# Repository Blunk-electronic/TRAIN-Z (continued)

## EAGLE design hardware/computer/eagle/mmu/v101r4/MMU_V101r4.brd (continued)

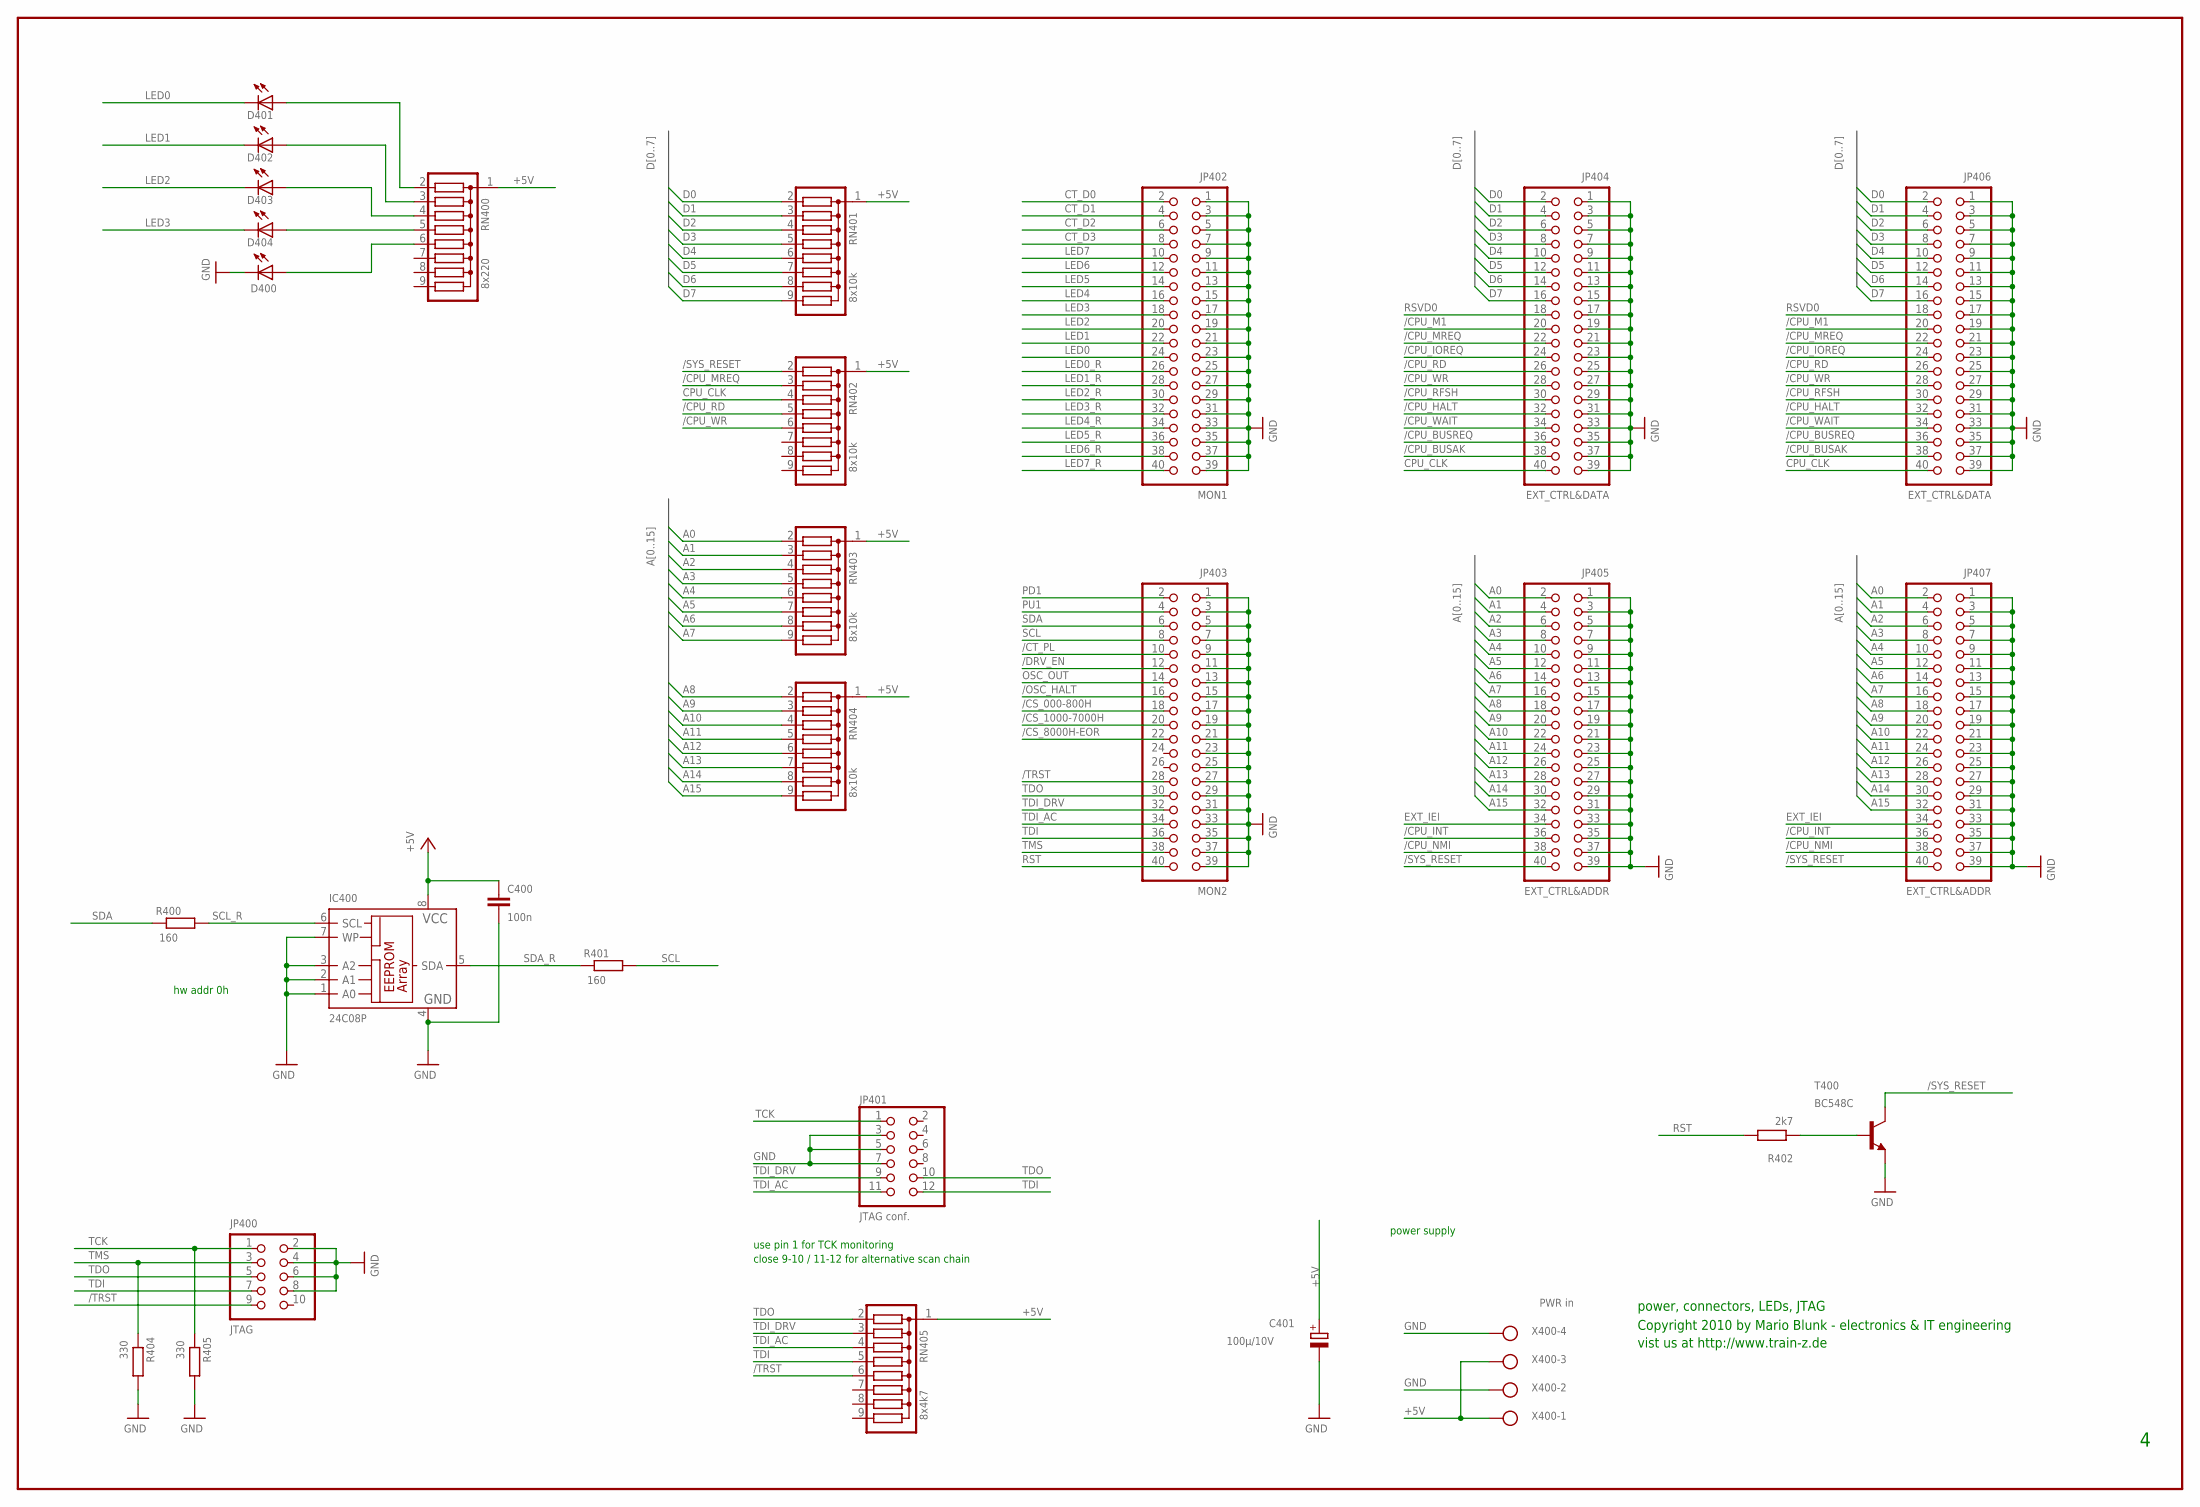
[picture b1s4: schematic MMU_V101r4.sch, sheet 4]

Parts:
C400: 100n; C050-030X075
C401: 100µ/10V; E2,5-7
D400, D401, D402, D403, D404: LED5MM
IC400: 24C08P; DIL8
JP400: JTAG; 2X05
JP401: JTAG conf.; 2X06
JP402: MON1; 2X20
JP403: MON2; 2X20
JP404, JP406: EXT_CTRL&DATA; 2X20
JP405, JP407: EXT_CTRL&ADDR; 2X20
R400, R401: 160; 0207/10
R402: 2k7; 0207/10
R404, R405: 330; 0207/10
RN400: 8x220; SIL9
RN401, RN402, RN403, RN404: 8x10k; SIL9
RN405: 8x4k7; SIL9
T400: BC548C; TO92
X400: PWR in; W237-4

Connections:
+5V: C400.1, C401.+, IC400.8 (VCC), RN400.1, RN401.1, RN402.1, RN403.1, RN404.1, RN405.1, X400.1, X400.3; also elsewhere on the board
/CPU_BUSAK: JP404.38, JP406.38
/CPU_BUSREQ: JP404.36, JP406.36
/CPU_HALT: JP404.32, JP406.32
/CPU_INT: JP405.36, JP407.36
/CPU_IOREQ: JP404.24, JP406.24
/CPU_M1: JP404.20, JP406.20
/CPU_MREQ: JP404.22, JP406.22, RN402.3; also elsewhere on the board
/CPU_NMI: JP405.38, JP407.38
/CPU_RD: JP404.26, JP406.26, RN402.5; also elsewhere on the board
/CPU_RFSH: JP404.30, JP406.30
/CPU_WAIT: JP404.34, JP406.34
/CPU_WR: JP404.28, JP406.28, RN402.6; also elsewhere on the board
/CS_000-800H: JP403.18; also elsewhere on the board
/CS_1000-7000H: JP403.20; also elsewhere on the board
/CS_8000H-EOR: JP403.22; also elsewhere on the board
/CT_PL: JP403.10; also elsewhere on the board
/DRV_EN: JP403.12; also elsewhere on the board
/OSC_HALT: JP403.16; also elsewhere on the board
/SYS_RESET: JP405.40, JP407.40, RN402.2, T400.3 (C); also elsewhere on the board
/TRST: JP400.9, JP403.28, RN405.6
A0: JP405.2, JP407.2, RN403.2; also elsewhere on the board
A1: JP405.4, JP407.4, RN403.3; also elsewhere on the board
A2: JP405.6, JP407.6, RN403.4; also elsewhere on the board
A3: JP405.8, JP407.8, RN403.5; also elsewhere on the board
A4: JP405.10, JP407.10, RN403.6; also elsewhere on the board
A5: JP405.12, JP407.12, RN403.7; also elsewhere on the board
A6: JP405.14, JP407.14, RN403.8; also elsewhere on the board
A7: JP405.16, JP407.16, RN403.9; also elsewhere on the board
A8: JP405.18, JP407.18, RN404.2; also elsewhere on the board
A9: JP405.20, JP407.20, RN404.3; also elsewhere on the board
A10: JP405.22, JP407.22, RN404.4; also elsewhere on the board
A11: JP405.24, JP407.24, RN404.5; also elsewhere on the board
A12: JP405.26, JP407.26, RN404.6; also elsewhere on the board
A13: JP405.28, JP407.28, RN404.7; also elsewhere on the board
A14: JP405.30, JP407.30, RN404.8; also elsewhere on the board
A15: JP405.32, JP407.32, RN404.9; also elsewhere on the board
CPU_CLK: JP404.40, JP406.40, RN402.4; also elsewhere on the board
CT_D0: JP402.2; also elsewhere on the board
CT_D1: JP402.4; also elsewhere on the board
CT_D2: JP402.6; also elsewhere on the board
CT_D3: JP402.8; also elsewhere on the board
D0: JP404.2, JP406.2, RN401.2; also elsewhere on the board
D1: JP404.4, JP406.4, RN401.3; also elsewhere on the board
D2: JP404.6, JP406.6, RN401.4; also elsewhere on the board
D3: JP404.8, JP406.8, RN401.5; also elsewhere on the board
D4: JP404.10, JP406.10, RN401.6; also elsewhere on the board
D4_A: D400.A, RN400.6
D5: JP404.12, JP406.12, RN401.7; also elsewhere on the board
D6: JP404.14, JP406.14, RN401.8; also elsewhere on the board
D7: JP404.16, JP406.16, RN401.9; also elsewhere on the board
EXT_IEI: JP405.34, JP407.34
GND: C400.2, C401.-, D400.K (C), IC400.1 (A0), IC400.2 (A1), IC400.3 (A2), IC400.4 (GND), IC400.7 (WP), JP400.2, JP400.4, JP400.6, JP400.8, JP401.3, JP401.5, JP401.7, JP402.1, JP402.3, JP402.5, JP402.7, JP402.9, JP402.11, JP402.13, JP402.15, JP402.17, JP402.19, JP402.21, JP402.23, JP402.25, JP402.27, JP402.29, JP402.31, JP402.33, JP402.35, JP402.37, JP402.39, JP403.1, JP403.3, JP403.5, JP403.7, JP403.9, JP403.11, JP403.13, JP403.15, JP403.17, JP403.19, JP403.21, JP403.23, JP403.25, JP403.27, JP403.29, JP403.31, JP403.33, JP403.35, JP403.37, JP403.39, JP404.1, JP404.3, JP404.5, JP404.7, JP404.9, JP404.11, JP404.13, JP404.15, JP404.17, JP404.19, JP404.21, JP404.23, JP404.25, JP404.27, JP404.29, JP404.31, JP404.33, JP404.35, JP404.37, JP404.39, JP405.1, JP405.3, JP405.5, JP405.7, JP405.9, JP405.11, JP405.13, JP405.15, JP405.17, JP405.19, JP405.21, JP405.23, JP405.25, JP405.27, JP405.29, JP405.31, JP405.33, JP405.35, JP405.37, JP405.39, JP406.1, JP406.3, JP406.5, JP406.7, JP406.9, JP406.11, JP406.13, JP406.15, JP406.17, JP406.19, JP406.21, JP406.23, JP406.25, JP406.27, JP406.29, JP406.31, JP406.33, JP406.35, JP406.37, JP406.39, JP407.1, JP407.3, JP407.5, JP407.7, JP407.9, JP407.11, JP407.13, JP407.15, JP407.17, JP407.19, JP407.21, JP407.23, JP407.25, JP407.27, JP407.29, JP407.31, JP407.33, JP407.35, JP407.37, JP407.39, R404.2, R405.2, T400.1 (E), X400.2, X400.4; also elsewhere on the board
LED0: D401.K (C), JP402.24; also elsewhere on the board
LED0_K: D401.A, RN400.2
LED0_R: JP402.26; also elsewhere on the board
LED1: D402.K (C), JP402.22; also elsewhere on the board
LED1_K: D402.A, RN400.3
LED1_R: JP402.28; also elsewhere on the board
LED2: D403.K (C), JP402.20; also elsewhere on the board
LED2_K: D403.A, RN400.4
LED2_R: JP402.30; also elsewhere on the board
LED3: D404.K (C), JP402.18; also elsewhere on the board
LED3_K: D404.A, RN400.5
LED3_R: JP402.32; also elsewhere on the board
LED4: JP402.16; also elsewhere on the board
LED4_R: JP402.34; also elsewhere on the board
LED5: JP402.14; also elsewhere on the board
LED5_R: JP402.36; also elsewhere on the board
LED6: JP402.12; also elsewhere on the board
LED6_R: JP402.38; also elsewhere on the board
LED7: JP402.10; also elsewhere on the board
LED7_R: JP402.40; also elsewhere on the board
OSC_OUT: JP403.14; also elsewhere on the board
PD1: JP403.2; also elsewhere on the board
PU1: JP403.4; also elsewhere on the board
RST: JP403.40, R402.2; also elsewhere on the board
RSVD0: JP404.18, JP406.18
SCL: JP403.8, R401.2; also elsewhere on the board
SCL_R: IC400.6 (SCL), R400.2
SDA: JP403.6, R400.1; also elsewhere on the board
SDA_R: IC400.5 (SDA), R401.1
T2_B: R402.1, T400.2 (B)
TCK: JP400.1, JP401.1, R405.1; also elsewhere on the board
TDI: JP400.7, JP401.12, JP403.36, RN405.5; also elsewhere on the board
TDI_AC: JP401.11, JP403.34, RN405.4; also elsewhere on the board
TDI_DRV: JP401.9, JP403.32, RN405.3; also elsewhere on the board
TDO: JP400.5, JP401.10, JP403.30, RN405.2; also elsewhere on the board
TMS: JP400.3, JP403.38, R404.1; also elsewhere on the board

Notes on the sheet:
power, connectors, LEDs, JTAG
power supply
hw addr 0h
close 9-10 / 11-12 for alternative scan chain
use pin 1 for TCK monitoring
Copyright 2010 by Mario Blunk - electronics & IT engineering
vist us at http://www.train-z.de

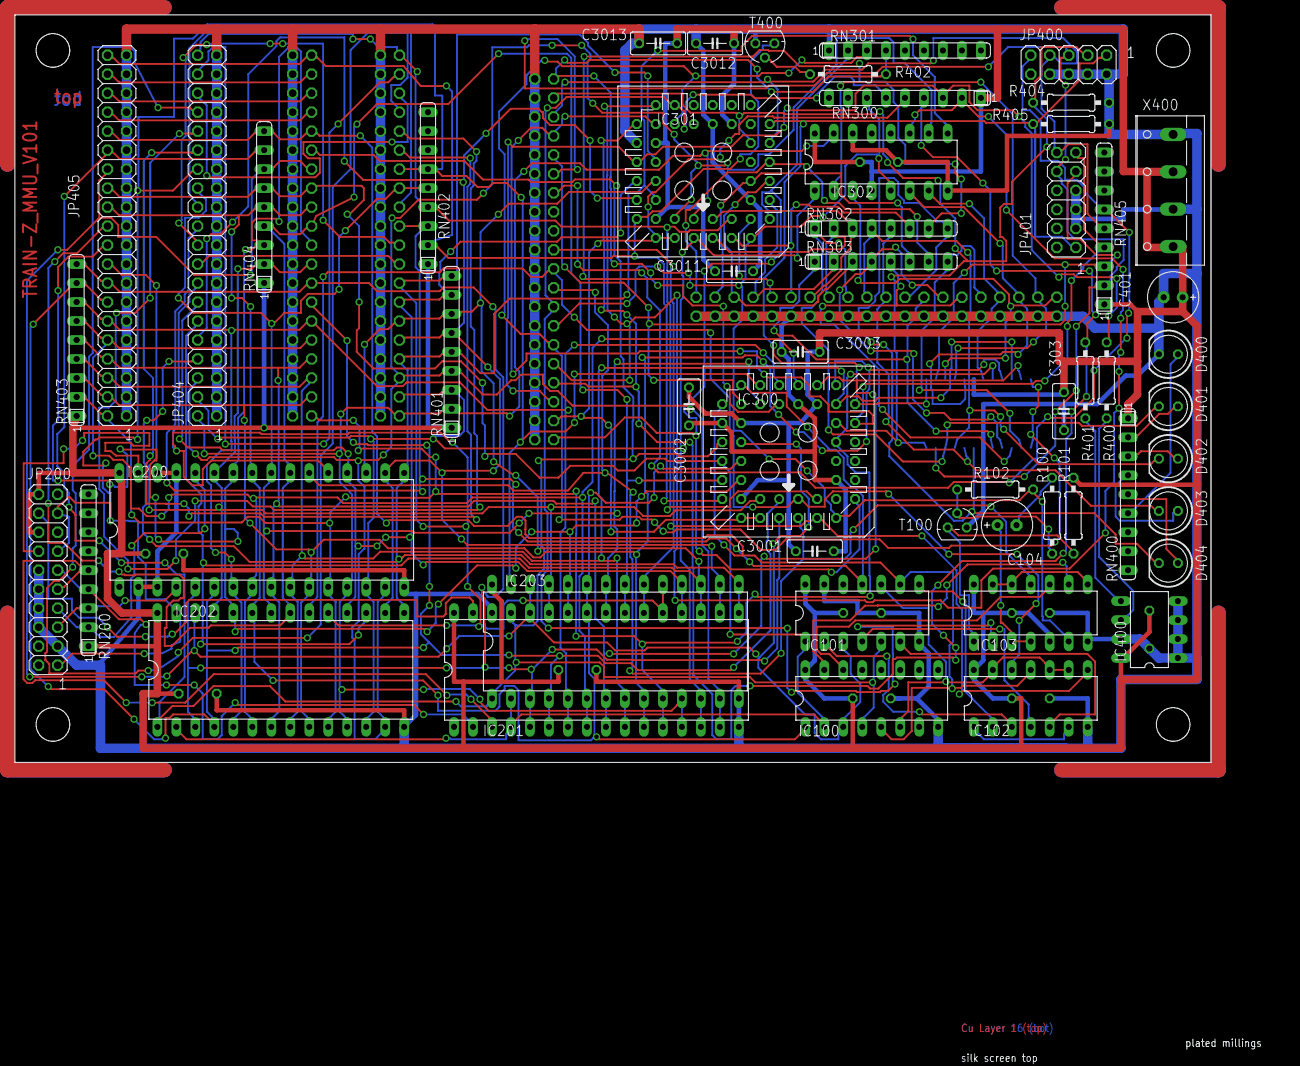
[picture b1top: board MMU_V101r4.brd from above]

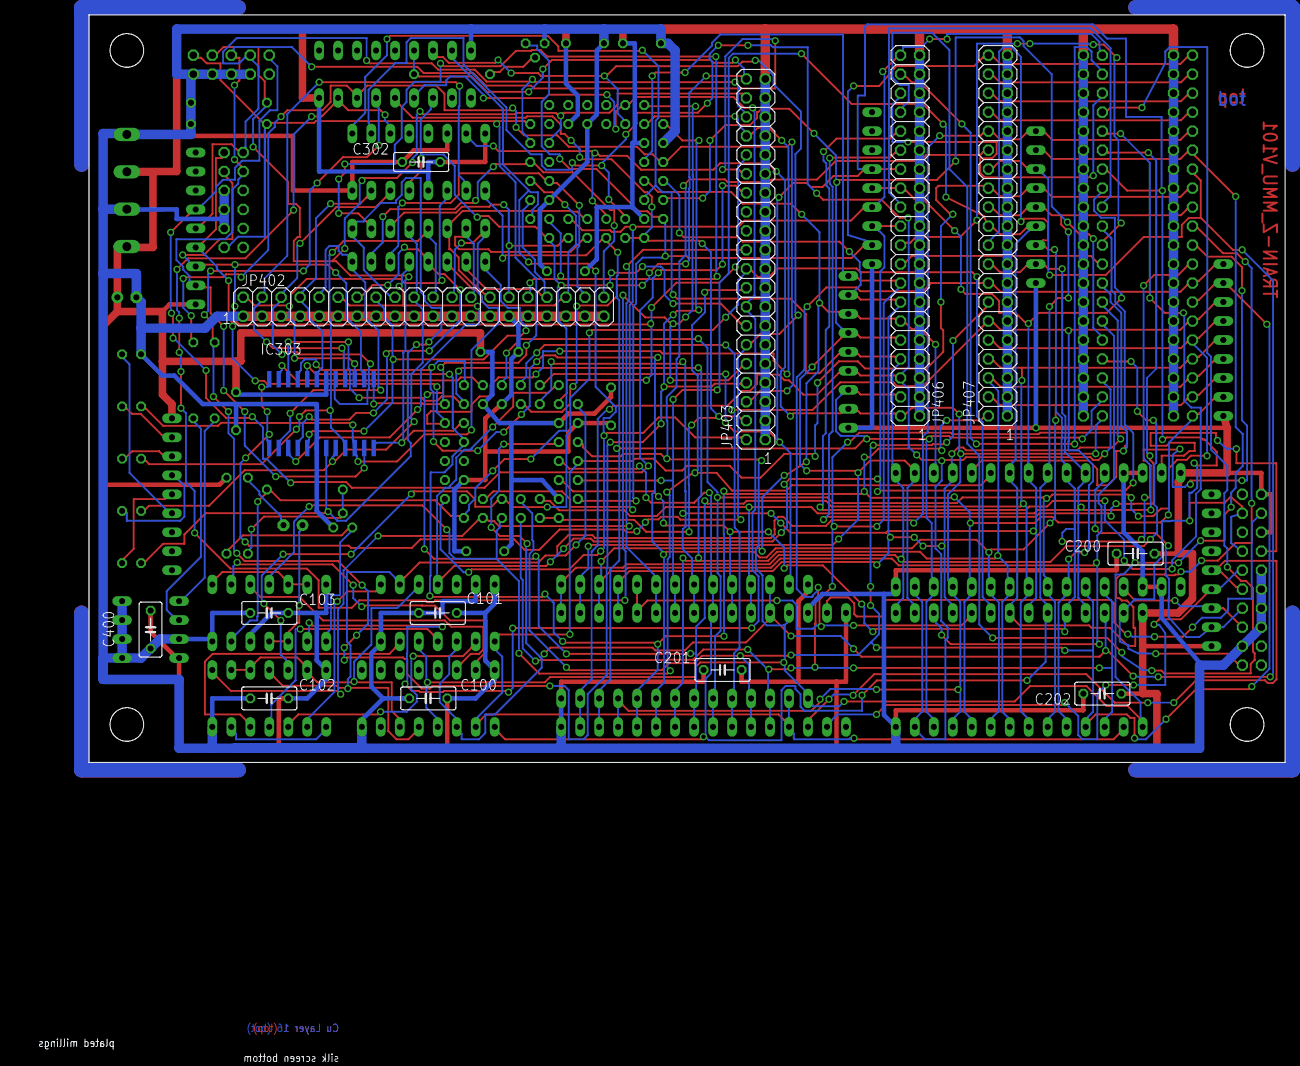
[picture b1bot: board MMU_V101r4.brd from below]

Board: 2 copper layers, 160.0 x 100.0 mm, 68 parts (14 on the bottom side), 108 nets.

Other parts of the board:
U$1: A4_LANDSCAPE

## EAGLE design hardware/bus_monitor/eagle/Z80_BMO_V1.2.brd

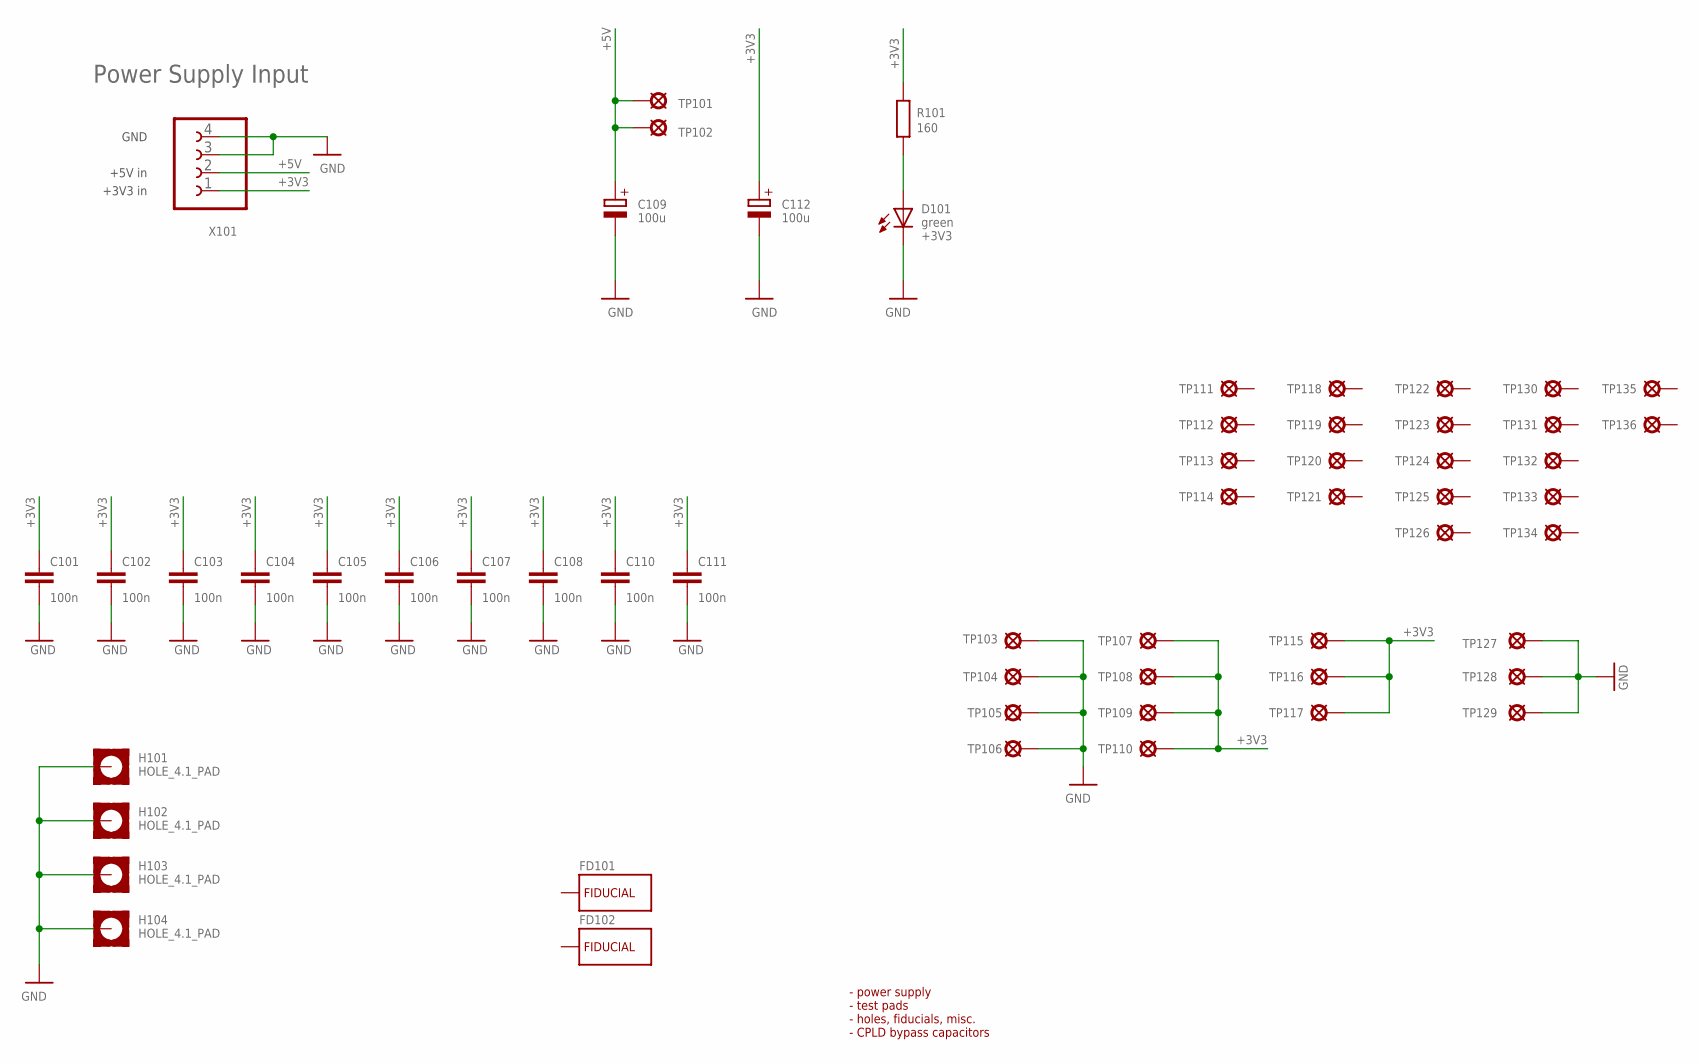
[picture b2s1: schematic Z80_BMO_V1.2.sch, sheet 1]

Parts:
C101, C102, C103, C104, C105, C106, C107, C108, C110, C111: 100n; S_0805; PART_CODE_BEL C_PAC_S_0805_VAL_100n
C109, C112: 100u; T_RADIAL_7MM_GRID_2.54MM; PART_CODE_BEL C_PAC_T_RADIAL_7mm_GRID_2.54mm_VAL_100u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
D101: green; T_LED_3MM; PART_CODE_BEL LED_PAC_T_3mm_VAL_green
FD101, FD102: FIDUCIAL_CROSSHAIR; CROSSHAIR
H101, H102, H103, H104: HOLE_4.1_PAD; 4.1_PAD
R101: 160; T_0207_GRID10MM; PART_CODE_BEL R_PAC_T_0207_GRID10mm_VAL_160
TP101, TP102, TP103, TP104, TP105, TP106, TP107, TP108, TP109, TP110, TP111, TP112, TP113, TP114, TP115, TP116, TP117, TP118, TP119, TP120, TP121, TP122, TP123, TP124, TP125, TP126, TP127, TP128, TP129, TP130, TP131, TP132, TP133, TP134, TP135, TP136: TEST_POINT_T_SMALL; T_TEST_POINT_SMALL
X101: CLAMP_1X4-T-5MM; T_WIRE_CLAMP_1X4_5MM

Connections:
3V3_LED_A: D101.A, R101.1
+3V3: C101.1, C102.1, C103.1, C104.1, C105.1, C106.1, C107.1, C108.1, C110.1, C111.1, C112.+, R101.2, TP107.1, TP108.1, TP109.1, TP110.1, TP115.1, TP116.1, TP117.1, X101.1; also elsewhere on the board
+5V: C109.+, TP101.1, TP102.1, X101.2
GND: C101.2, C102.2, C103.2, C104.2, C105.2, C106.2, C107.2, C108.2, C109.-, C110.2, C111.2, C112.-, D101.C, H101.H1, H102.H1, H103.H1, H104.H1, TP103.1, TP104.1, TP105.1, TP106.1, TP127.1, TP128.1, TP129.1, X101.3, X101.4; also elsewhere on the board

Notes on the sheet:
+3V3 in
+5V in
GND
- power supply - test pads - holes, fiducials, misc. - CPLD bypass capacitors

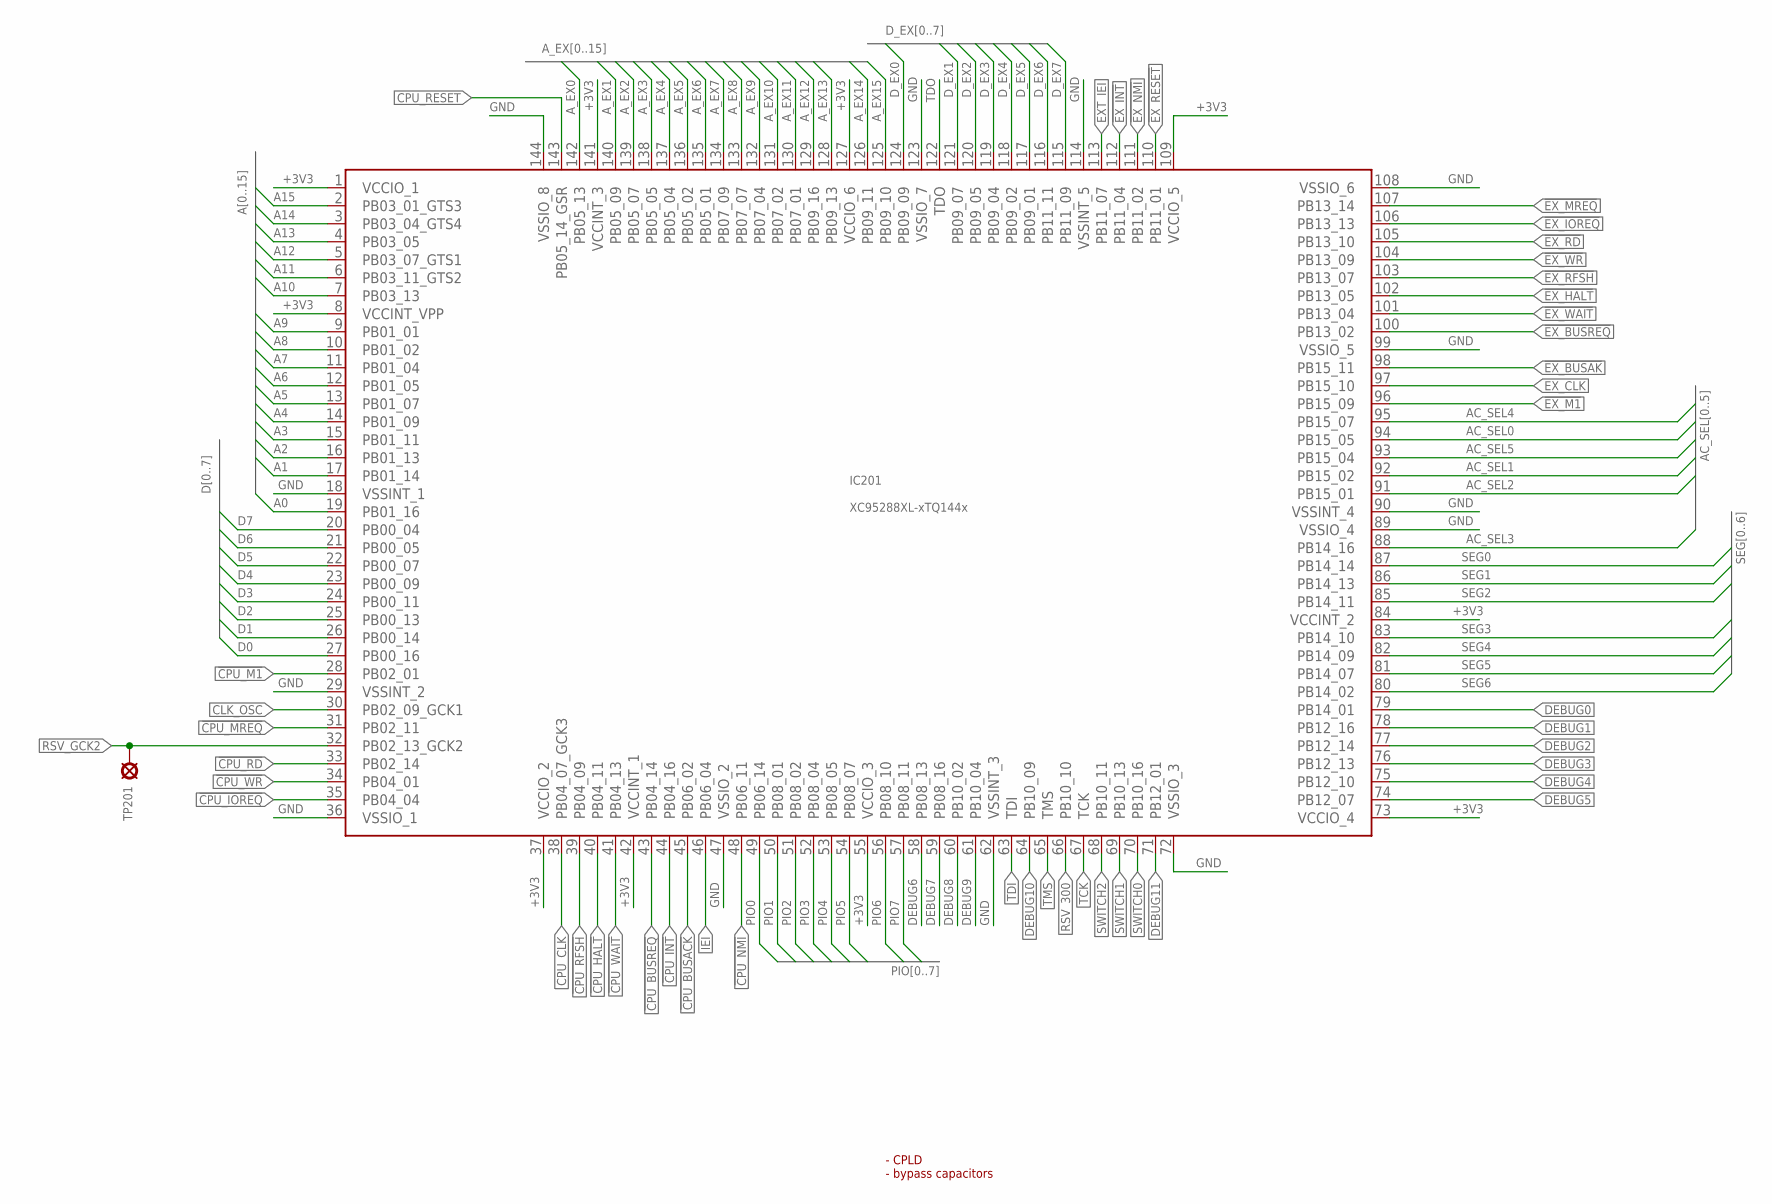
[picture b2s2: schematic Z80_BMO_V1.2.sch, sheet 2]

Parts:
IC201: XC95288XL-xTQ144x; S_TQFP144
TP201: TEST_POINT_T_SMALL; T_TEST_POINT_SMALL

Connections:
!CPU_BUSACK: IC201.45 (PB06_02); also elsewhere on the board
!CPU_BUSREQ: IC201.43 (PB04_14); also elsewhere on the board
!CPU_HALT: IC201.40 (PB04_11); also elsewhere on the board
!CPU_INT: IC201.44 (PB04_16); also elsewhere on the board
!CPU_IOREQ: IC201.35 (PB04_04); also elsewhere on the board
!CPU_M1: IC201.28 (PB02_01); also elsewhere on the board
!CPU_MREQ: IC201.31 (PB02_11); also elsewhere on the board
!CPU_NMI: IC201.48 (PB06_11); also elsewhere on the board
!CPU_RD: IC201.33 (PB02_14); also elsewhere on the board
!CPU_RFSH: IC201.39 (PB04_09); also elsewhere on the board
!CPU_WAIT: IC201.41 (PB04_13); also elsewhere on the board
!CPU_WR: IC201.34 (PB04_01); also elsewhere on the board
!EX_BUSAK: IC201.98 (PB15_11); also elsewhere on the board
!EX_BUSREQ: IC201.100 (PB13_02); also elsewhere on the board
!EX_HALT: IC201.102 (PB13_05); also elsewhere on the board
!EX_INT: IC201.112 (PB11_04); also elsewhere on the board
!EX_IOREQ: IC201.106 (PB13_13); also elsewhere on the board
!EX_M1: IC201.96 (PB15_09); also elsewhere on the board
!EX_MREQ: IC201.107 (PB13_14); also elsewhere on the board
!EX_NMI: IC201.111 (PB11_02); also elsewhere on the board
!EX_RD: IC201.105 (PB13_10); also elsewhere on the board
!EX_RESET: IC201.110 (PB11_01); also elsewhere on the board
!EX_RFSH: IC201.103 (PB13_07); also elsewhere on the board
!EX_WAIT: IC201.101 (PB13_04); also elsewhere on the board
!EX_WR: IC201.104 (PB13_09); also elsewhere on the board
+3V3: IC201.1 (VCCIO_1), IC201.8 (VCCINT_VPP), IC201.37 (VCCIO_2), IC201.42 (VCCINT_1), IC201.55 (VCCIO_3), IC201.73 (VCCIO_4), IC201.84 (VCCINT_2), IC201.109 (VCCIO_5), IC201.127 (VCCIO_6), IC201.141 (VCCINT_3); also elsewhere on the board
A0: IC201.19 (PB01_16); also elsewhere on the board
A1: IC201.17 (PB01_14); also elsewhere on the board
A2: IC201.16 (PB01_13); also elsewhere on the board
A3: IC201.15 (PB01_11); also elsewhere on the board
A4: IC201.14 (PB01_09); also elsewhere on the board
A5: IC201.13 (PB01_07); also elsewhere on the board
A6: IC201.12 (PB01_05); also elsewhere on the board
A7: IC201.11 (PB01_04); also elsewhere on the board
A8: IC201.10 (PB01_02); also elsewhere on the board
A9: IC201.9 (PB01_01); also elsewhere on the board
A10: IC201.7 (PB03_13); also elsewhere on the board
A11: IC201.6 (PB03_11_GTS2); also elsewhere on the board
A12: IC201.5 (PB03_07_GTS1); also elsewhere on the board
A13: IC201.4 (PB03_05); also elsewhere on the board
A14: IC201.3 (PB03_04_GTS4); also elsewhere on the board
A15: IC201.2 (PB03_01_GTS3); also elsewhere on the board
AC_SEL0: IC201.94 (PB15_05); also elsewhere on the board
AC_SEL1: IC201.92 (PB15_02); also elsewhere on the board
AC_SEL2: IC201.91 (PB15_01); also elsewhere on the board
AC_SEL3: IC201.88 (PB14_16); also elsewhere on the board
AC_SEL4: IC201.95 (PB15_07); also elsewhere on the board
AC_SEL5: IC201.93 (PB15_04); also elsewhere on the board
A_EX0: IC201.142 (PB05_13); also elsewhere on the board
A_EX1: IC201.140 (PB05_09); also elsewhere on the board
A_EX2: IC201.139 (PB05_07); also elsewhere on the board
A_EX3: IC201.138 (PB05_05); also elsewhere on the board
A_EX4: IC201.137 (PB05_04); also elsewhere on the board
A_EX5: IC201.136 (PB05_02); also elsewhere on the board
A_EX6: IC201.135 (PB05_01); also elsewhere on the board
A_EX7: IC201.134 (PB07_09); also elsewhere on the board
A_EX8: IC201.133 (PB07_07); also elsewhere on the board
A_EX9: IC201.132 (PB07_04); also elsewhere on the board
A_EX10: IC201.131 (PB07_02); also elsewhere on the board
A_EX11: IC201.130 (PB07_01); also elsewhere on the board
A_EX12: IC201.129 (PB09_16); also elsewhere on the board
A_EX13: IC201.128 (PB09_13); also elsewhere on the board
A_EX14: IC201.126 (PB09_11); also elsewhere on the board
A_EX15: IC201.125 (PB09_10); also elsewhere on the board
CLK_OSC: IC201.30 (PB02_09_GCK1); also elsewhere on the board
CPU_CLK: IC201.38 (PB04_07_GCK3); also elsewhere on the board
CPU_RESET: IC201.143 (PB05_14_GSR); also elsewhere on the board
D0: IC201.27 (PB00_16); also elsewhere on the board
D1: IC201.26 (PB00_14); also elsewhere on the board
D2: IC201.25 (PB00_13); also elsewhere on the board
D3: IC201.24 (PB00_11); also elsewhere on the board
D4: IC201.23 (PB00_09); also elsewhere on the board
D5: IC201.22 (PB00_07); also elsewhere on the board
D6: IC201.21 (PB00_05); also elsewhere on the board
D7: IC201.20 (PB00_04); also elsewhere on the board
DEBUG0: IC201.79 (PB14_01); also elsewhere on the board
DEBUG1: IC201.78 (PB12_16); also elsewhere on the board
DEBUG2: IC201.77 (PB12_14); also elsewhere on the board
DEBUG3: IC201.76 (PB12_13); also elsewhere on the board
DEBUG4: IC201.75 (PB12_10); also elsewhere on the board
DEBUG5: IC201.74 (PB12_07); also elsewhere on the board
DEBUG6: IC201.58 (PB08_13); also elsewhere on the board
DEBUG7: IC201.59 (PB08_16); also elsewhere on the board
DEBUG8: IC201.60 (PB10_02); also elsewhere on the board
DEBUG9: IC201.61 (PB10_04); also elsewhere on the board
DEBUG10: IC201.64 (PB10_09); also elsewhere on the board
DEBUG11: IC201.71 (PB12_01); also elsewhere on the board
D_EX0: IC201.124 (PB09_09); also elsewhere on the board
D_EX1: IC201.121 (PB09_07); also elsewhere on the board
D_EX2: IC201.120 (PB09_05); also elsewhere on the board
D_EX3: IC201.119 (PB09_04); also elsewhere on the board
D_EX4: IC201.118 (PB09_02); also elsewhere on the board
D_EX5: IC201.117 (PB09_01); also elsewhere on the board
D_EX6: IC201.116 (PB11_11); also elsewhere on the board
D_EX7: IC201.115 (PB11_09); also elsewhere on the board
EXT_IEI: IC201.113 (PB11_07); also elsewhere on the board
EX_CLK: IC201.97 (PB15_10); also elsewhere on the board
GND: IC201.18 (VSSINT_1), IC201.29 (VSSINT_2), IC201.36 (VSSIO_1), IC201.47 (VSSIO_2), IC201.62 (VSSINT_3), IC201.72 (VSSIO_3), IC201.89 (VSSIO_4), IC201.90 (VSSINT_4), IC201.99 (VSSIO_5), IC201.108 (VSSIO_6), IC201.114 (VSSINT_5), IC201.123 (VSSIO_7), IC201.144 (VSSIO_8); also elsewhere on the board
IEI: IC201.46 (PB06_04); also elsewhere on the board
PIO0: IC201.49 (PB06_14); also elsewhere on the board
PIO1: IC201.50 (PB08_01); also elsewhere on the board
PIO2: IC201.51 (PB08_02); also elsewhere on the board
PIO3: IC201.52 (PB08_04); also elsewhere on the board
PIO4: IC201.53 (PB08_05); also elsewhere on the board
PIO5: IC201.54 (PB08_07); also elsewhere on the board
PIO6: IC201.56 (PB08_10); also elsewhere on the board
PIO7: IC201.57 (PB08_11); also elsewhere on the board
RSV_300: IC201.66 (PB10_10); also elsewhere on the board
RSV_GCK2: IC201.32 (PB02_13_GCK2), TP201.1; also elsewhere on the board
SEG0: IC201.87 (PB14_14); also elsewhere on the board
SEG1: IC201.86 (PB14_13); also elsewhere on the board
SEG2: IC201.85 (PB14_11); also elsewhere on the board
SEG3: IC201.83 (PB14_10); also elsewhere on the board
SEG4: IC201.82 (PB14_09); also elsewhere on the board
SEG5: IC201.81 (PB14_07); also elsewhere on the board
SEG6: IC201.80 (PB14_02); also elsewhere on the board
SWITCH0: IC201.70 (PB10_16); also elsewhere on the board
SWITCH1: IC201.69 (PB10_13); also elsewhere on the board
SWITCH2: IC201.68 (PB10_11); also elsewhere on the board
TCK: IC201.67 (TCK); also elsewhere on the board
TDI: IC201.63 (TDI); also elsewhere on the board
TDO: IC201.122 (TDO); also elsewhere on the board
TMS: IC201.65 (TMS); also elsewhere on the board

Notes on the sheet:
- CPLD - bypass capacitors

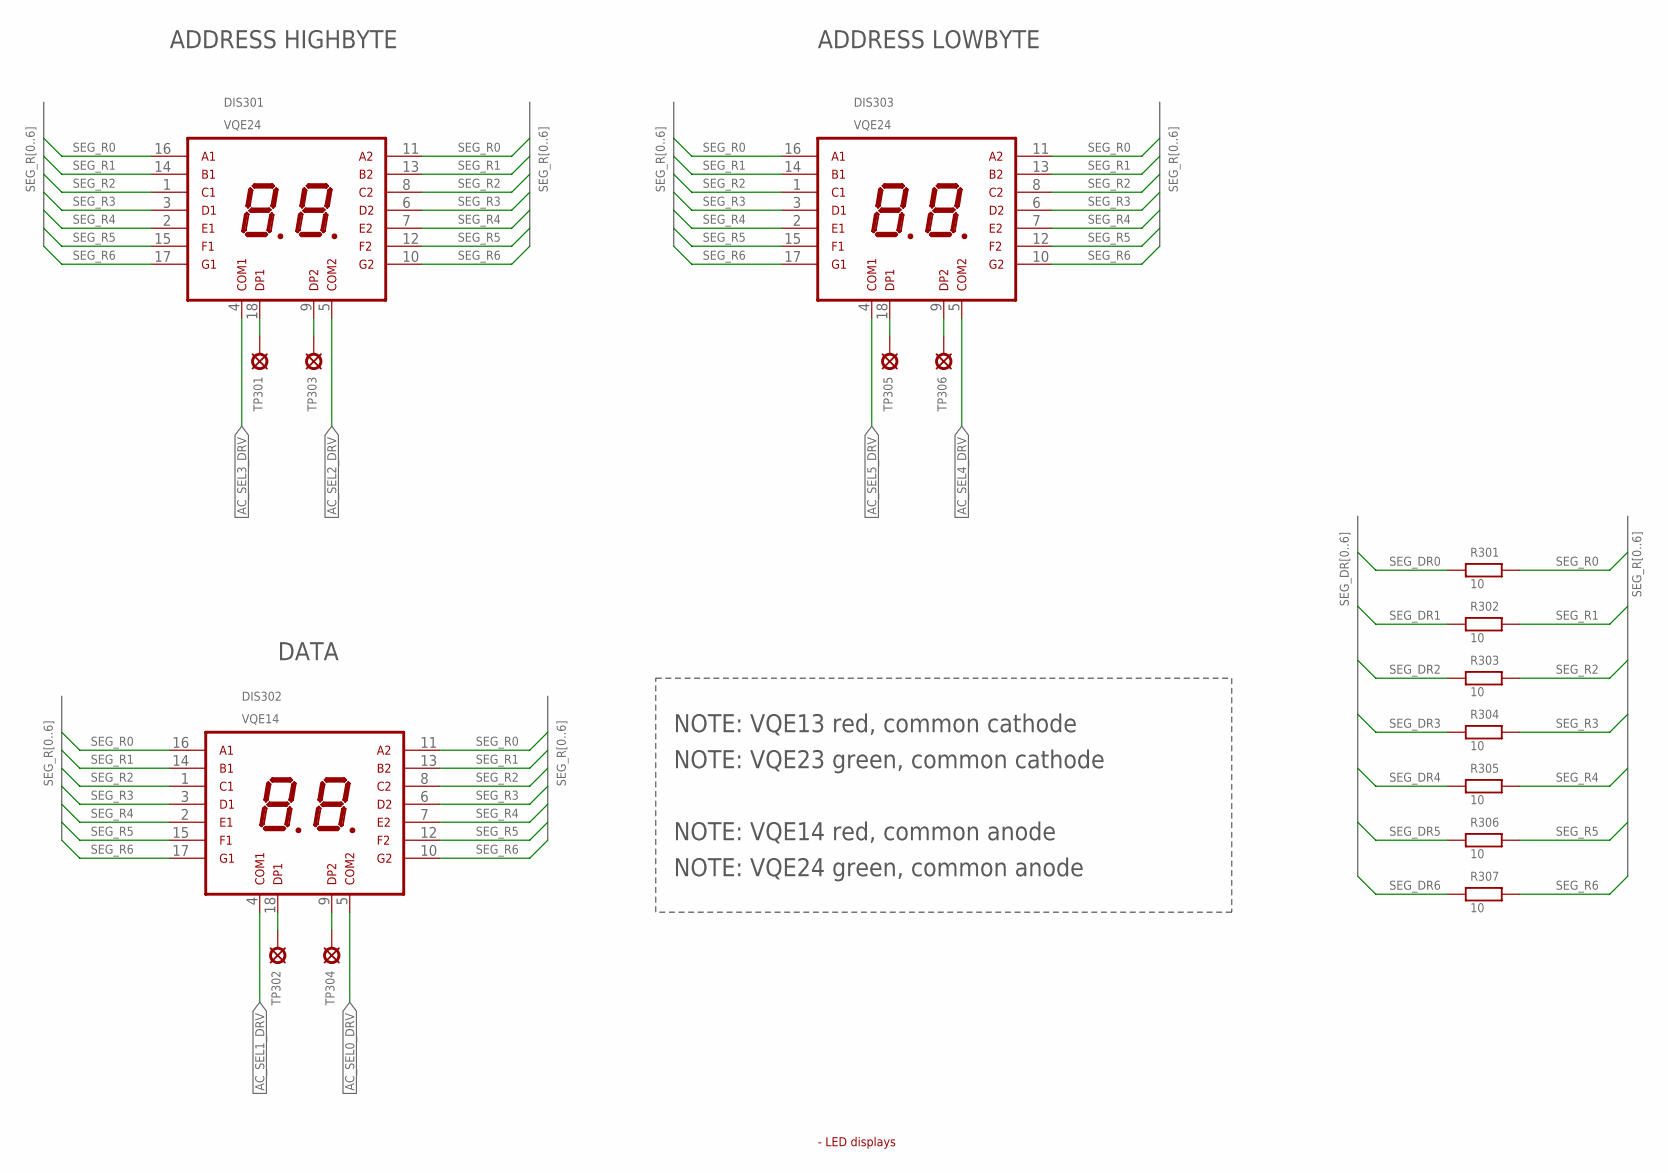
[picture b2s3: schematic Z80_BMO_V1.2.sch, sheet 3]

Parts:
DIS301, DIS303: VQE24; T_VQE_XX_2DIGIT; PART_CODE_BEL DIS_T_PAC_VQExx_2DIGIT_VAL_VQE24
DIS302: VQE14; T_VQE_XX_2DIGIT; PART_CODE_BEL DIS_T_PAC_VQExx_2DIGIT_VAL_VQE14
R301, R302, R303, R304, R305, R306, R307: 10; T_0207_GRID10MM; PART_CODE_BEL R_PAC_T_0207_GRID10mm_VAL_10
TP301, TP302, TP303, TP304, TP305, TP306: TEST_POINT_T_SMALL; T_TEST_POINT_SMALL

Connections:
AC_SEL0_DRV: DIS302.5 (COM2); also elsewhere on the board
AC_SEL1_DRV: DIS302.4 (COM1); also elsewhere on the board
AC_SEL2_DRV: DIS301.5 (COM2); also elsewhere on the board
AC_SEL3_DRV: DIS301.4 (COM1); also elsewhere on the board
AC_SEL4_DRV: DIS303.5 (COM2); also elsewhere on the board
AC_SEL5_DRV: DIS303.4 (COM1); also elsewhere on the board
unnamed: DIS303.9 (DP2), TP306.1
unnamed: DIS303.18 (DP1), TP305.1
unnamed: DIS301.9 (DP2), TP303.1
unnamed: DIS301.18 (DP1), TP301.1
unnamed: DIS302.9 (DP2), TP304.1
unnamed: DIS302.18 (DP1), TP302.1
SEG_DR0: R301.2; also elsewhere on the board
SEG_DR1: R302.2; also elsewhere on the board
SEG_DR2: R303.2; also elsewhere on the board
SEG_DR3: R304.2; also elsewhere on the board
SEG_DR4: R305.2; also elsewhere on the board
SEG_DR5: R306.2; also elsewhere on the board
SEG_DR6: R307.2; also elsewhere on the board
SEG_R0: DIS301.11 (A2), DIS301.16 (A1), DIS302.11 (A2), DIS302.16 (A1), DIS303.11 (A2), DIS303.16 (A1), R301.1
SEG_R1: DIS301.13 (B2), DIS301.14 (B1), DIS302.13 (B2), DIS302.14 (B1), DIS303.13 (B2), DIS303.14 (B1), R302.1
SEG_R2: DIS301.1 (C1), DIS301.8 (C2), DIS302.1 (C1), DIS302.8 (C2), DIS303.1 (C1), DIS303.8 (C2), R303.1
SEG_R3: DIS301.3 (D1), DIS301.6 (D2), DIS302.3 (D1), DIS302.6 (D2), DIS303.3 (D1), DIS303.6 (D2), R304.1
SEG_R4: DIS301.2 (E1), DIS301.7 (E2), DIS302.2 (E1), DIS302.7 (E2), DIS303.2 (E1), DIS303.7 (E2), R305.1
SEG_R5: DIS301.12 (F2), DIS301.15 (F1), DIS302.12 (F2), DIS302.15 (F1), DIS303.12 (F2), DIS303.15 (F1), R306.1
SEG_R6: DIS301.10 (G2), DIS301.17 (G1), DIS302.10 (G2), DIS302.17 (G1), DIS303.10 (G2), DIS303.17 (G1), R307.1

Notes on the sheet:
DATA
ADDRESS HIGHBYTE
ADDRESS LOWBYTE
NOTE: VQE13 red, common cathode
NOTE: VQE23 green, common cathode
NOTE: VQE14 red, common anode
NOTE: VQE24 green, common anode
- LED displays
